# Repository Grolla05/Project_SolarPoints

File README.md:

# 💡 Project Solar Points — Smart Lighting for Low-Infrastructure Areas

> Light where there’s no infrastructure. Safety through simplicity and efficiency.

---

## 🌙 O que é o Solar Points?

O **Solar Points** é um sistema de iluminação pública autônomo e inteligente pensado para locais com pouca ou nenhuma infraestrutura elétrica, como:

- Paradas de ônibus
- Vielas e ruas estreitas
- Praças públicas
- Regiões periféricas e isoladas
- Áreas externas de residências

O objetivo permanece o mesmo: aumentar a segurança e o bem-estar comunitário com uma solução de baixo custo, sustentável e de fácil manutenção.

---

## 🔁 Evolução do projeto: de totalmente analógico para arquitetura digital

Inicialmente o projeto foi concebido como **100% analógico** (apenas componentes discretos e circuitos analógicos). Com as necessidades de sensoriamento mais preciso, flexibilidade operacional e otimização de consumo, o projeto evoluiu para uma **arquitetura digital/híbrida** baseada em microcontrolador e periféricos.

Essa mudança preserva os princípios de simplicidade, robustez e baixo consumo, ao mesmo tempo que agrega capacidades importantes:

- **Leitura digital de sensores** (intensidade de luz, distância/presença)
- **Decisões e temporizações programáveis** via firmware leve
- **Gerenciamento inteligente de energia** (controle de conversores DC-DC, modos de sono)
- **Comunicação entre módulos** via I2C/GPIO quando necessário

> A imagem anexada ao repositório ilustra o bloco funcional do novo design: microcontrolador central, sensores de luz e distância, gerenciamento de energia, baterias e conversores DC-DC.

---

## ⚙️ Principais funcionalidades (atualizado)

- **Ativação automática** baseada em sensores de luminosidade e presença
- **Modos ajustáveis** via firmware (p.ex. sensibilidades, temporização)
- **Operação autônoma** com painéis solares e baterias
- **Gestão adequada de energia** com conversores DC-DC e técnicas de baixo consumo
- **Projeto modular e replicável** com possibilidade de atualização de firmware

---

## 🛠️ Tecnologias e componentes (atualizado)

- **Microcontrolador** (unidade central de controle) — responsável por leitura de sensores e lógica de acionamento
- **Sensor de luminosidade** (LDR/photodiode + ADC) — medida de intensidade luminosa
- **Sensor de distância/presença** (ultrassom/IR) — detectar passagem ou presença
- **Conversores DC-DC** (step-up/step-down) — fornecimento estável para LEDs e eletrônica
- **Gestão de energia / Power Management** (monitoramento de bateria, carregamento solar)
- **Bateria recarregável e painéis solares**
- **LEDs de potência** para iluminação pública
- **Interfaces**: GPIOs para sinalização/controle, I2C para sensores/power ICs quando aplicável

---

## 🔍 Diagrama funcional

O diagrama no repositório mostra os blocos principais interconectados:

- 1 — Baterias (alimentação)
- 4 — Power Management (monitoramento/carregador)
- 11 — Conversão DC-DC (alimentação dos LEDs e eletrônica)
- 2 — Microcontrolador (núcleo lógico)
- 5 — Medição de intensidade luminosa (sensor)
- 6 — Sensor de distância/presença
- 3 — LED de status / power

O microcontrolador realiza a lógica central: lê sensores (GPIOs/ADC/I2C), decide quando ligar os LEDs e controla os conversores para otimizar consumo.

---

## ✨ Aplicações no mundo real

O Solar Points continua ideal para iluminar pontos sem infraestrutura elétrica: pontos de ônibus, caminhos em áreas rurais, entradas de condomínios e outras localidades onde uma solução autônoma e resiliente faz diferença.

---

## 👥 Autores

Desenvolvido por:

- **Felipe Grolla Freitas** – Engenharia de Controle e Automação (PUC-Campinas)
- **Guilherme Oliveira Nogueira** – Engenharia de Controle e Automação (PUC-Campinas)
- **Giovanna Lima Salvagnini** – Engenharia de Controle e Automação (PUC-Campinas)
- **Henrique Spadaccia Chambó** – Engenharia de Controle e Automação (PUC-Campinas)

---

> 🧠 "A simplicidade, aliada a decisões digitais pontuais, amplia o impacto das soluções de engenharia em contextos reais."

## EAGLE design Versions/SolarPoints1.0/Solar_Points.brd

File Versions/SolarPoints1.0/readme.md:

# First version of the project (Solar Point with only analog circuit)
## Schematc circuit diagram

## BRD Circuit file

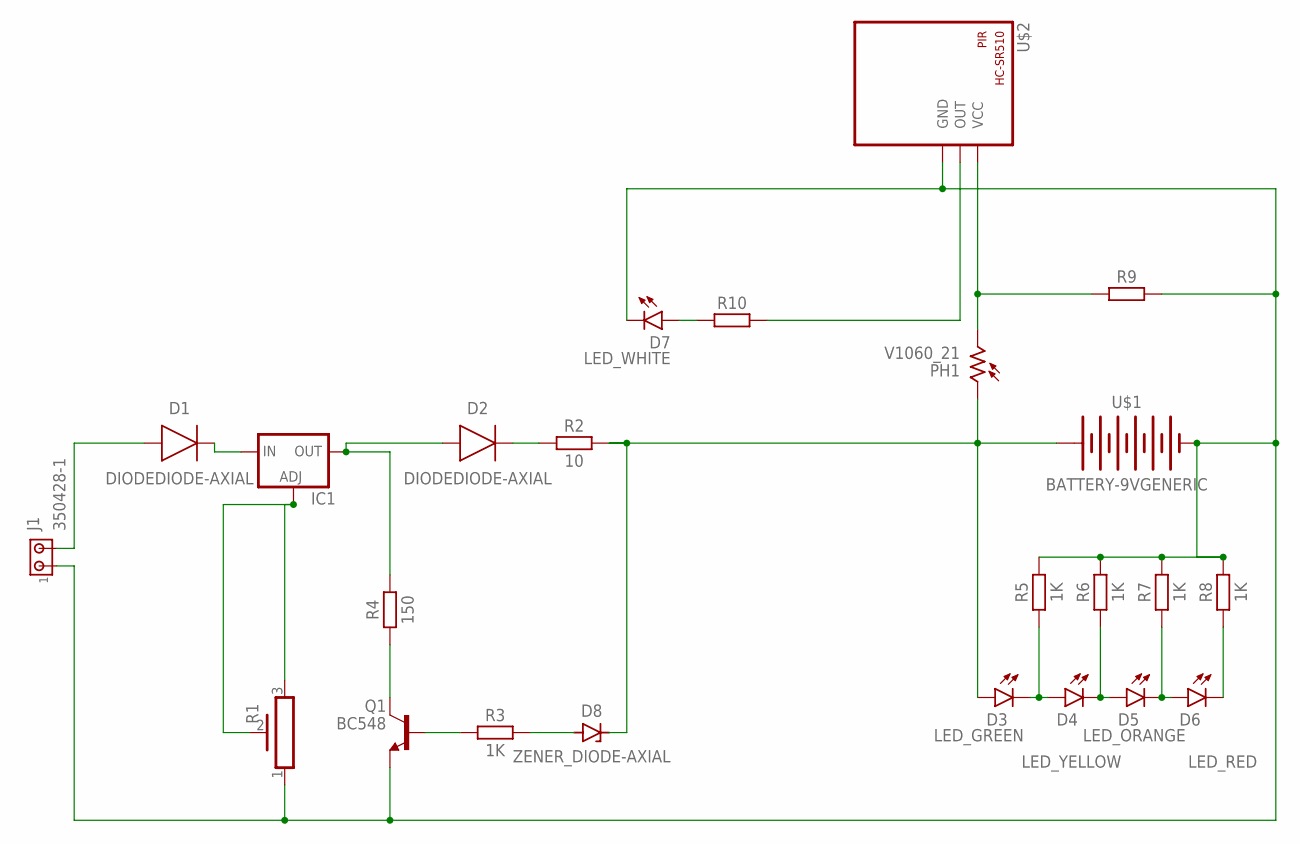
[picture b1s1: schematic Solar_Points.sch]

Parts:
D1, D2: DIODEDIODE-AXIAL; DIODE-AXIAL
D3: LED_GREEN; LEDRD254W60D565H860B_G
D4: LED_YELLOW; LEDRD254W60D565H860B_Y
D5: LED_ORANGE; LEDRD254W60D565H860B_O
D6: LED_RED; LEDRD254W60D565H860B
D7: LED_WHITE; LEDRD254W60D565H860B_W
D8: ZENER_DIODE-AXIAL; DIODE-AXIAL
IC1: LM317TL; 317TL
J1: 350428-1
PH1: V1060_21; TO-5_V10
Q1: BC548; TO92
R1: POT_PV36Z; PV36Z
R2: 10; RESAD1176W63L850D250B
R3, R5, R6, R7, R8: 1K; RESAD1176W63L850D250B
R4: 150; RESAD1176W63L850D250B
R9, R10: RESISTOR__AXIAL-11.7MM-PITCH; RESAD1176W63L850D250B
U$1: BATTERY-9VGENERIC; BATTERY-GENERIC
U$2: HC-SR501

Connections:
unnamed: D1.1 (A), J1.2
unnamed: Q1.1 (C), R4.1
unnamed: Q1.2 (B), R3.1
unnamed: D1.2 (C), IC1.3 (IN)
unnamed: D3.2 (C), D4.1 (A), R5.1
unnamed: D2.2 (C), R2.1
unnamed: D3.1 (A), D8.2 (C), PH1.1, R2.2, U$1.+
unnamed: D7.1 (A), R10.1
unnamed: D4.2 (C), D5.1 (A), R6.1
unnamed: PH1.2, R9.1, U$2.VCC
unnamed: D5.2 (C), D6.1 (A), R7.1
unnamed: R10.2, U$2.OUT
unnamed: D6.2 (C), R8.1
unnamed: D7.2 (C), J1.1, Q1.3 (E), R1.1, R5.2, R6.2, R7.2, R8.2, R9.2, U$1.-, U$2.GND
unnamed: D8.1 (A), R3.2
unnamed: D2.1 (A), IC1.2 (OUT), R4.2
unnamed: IC1.1 (ADJ), R1.2, R1.3

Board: 2 copper layers, 24 parts (0 on the bottom side), 17 nets, no tracks yet.

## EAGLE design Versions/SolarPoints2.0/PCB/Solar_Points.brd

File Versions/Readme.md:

## This folder serves to archive all iterations of the project since 2025.

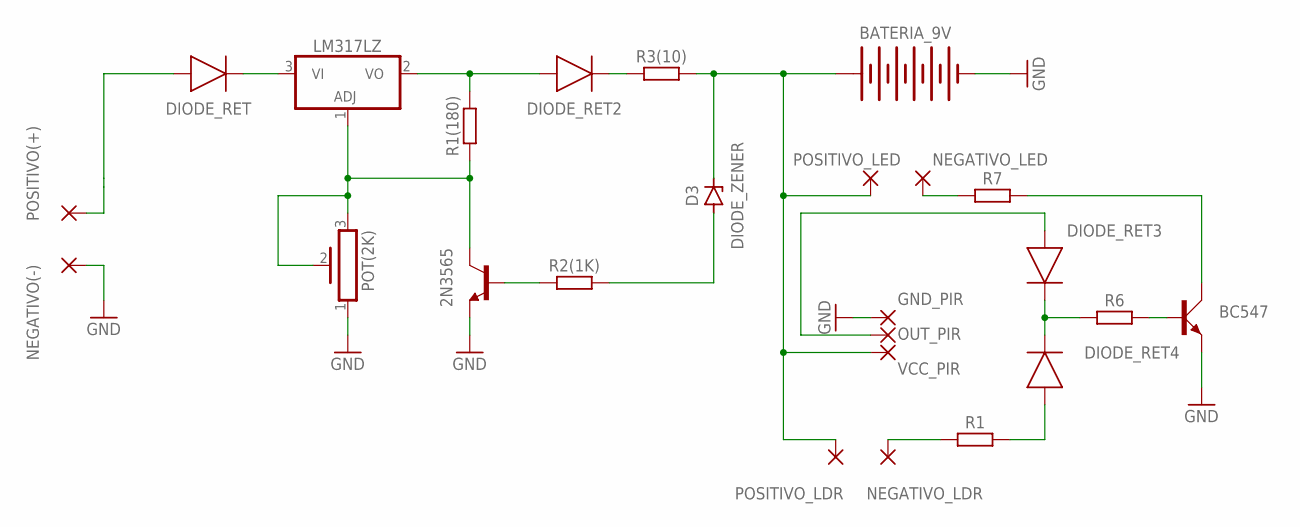
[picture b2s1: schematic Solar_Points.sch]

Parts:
2N3565: 2N3565; TO92
BATERIA_9V: BATTERY-9VGENERIC; BATTERY-GENERIC
BC547: BC547; SOT54A
D3: DIODE_ZENER; DIODE-AXIAL
DIODE_RET, DIODE_RET2, DIODE_RET3, DIODE_RET4: DIODEDIODE-AXIAL; DIODE-AXIAL
GND_PIR: 1,6/0,8
LM317LZ: LM317LZ; TO92
NEGATIVO(-): 3,81/1,4
NEGATIVO_LDR: 1,6/0,8
NEGATIVO_LED: 2,15/1,0
OUT_PIR: 1,6/0,8
POSITIVO(+): 3,81/1,4
POSITIVO_LDR: 1,6/0,8
POSITIVO_LED: 2,15/1,0
POT(2K): POT_HA-06; HA-06-SM065
R1, R1(180), R2(1K), R3(10), R6, R7: RESISTOR_AXIAL-10.16MM-PITCH; RESAD1016W63L850D250B
VCC_PIR: 1,6/0,8

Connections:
GND: 2N3565.3 (E), BATERIA_9V.-, BC547.E, GND_PIR.1, NEGATIVO(-).1, POT(2K).1
unnamed: DIODE_RET.1 (A), POSITIVO(+).1
unnamed: DIODE_RET.2 (C), LM317LZ.3 (VI)
unnamed: 2N3565.1 (C), LM317LZ.1 (ADJ), POT(2K).2, POT(2K).3, R1(180).1
unnamed: DIODE_RET2.1 (A), LM317LZ.2 (VO), R1(180).2
unnamed: DIODE_RET2.2 (C), R3(10).2
unnamed: BATERIA_9V.+, D3.2 (C), POSITIVO_LDR.1, POSITIVO_LED.1, R3(10).1, VCC_PIR.1
unnamed: D3.1 (A), R2(1K).1
unnamed: 2N3565.2 (B), R2(1K).2
unnamed: DIODE_RET3.1 (A), OUT_PIR.1
unnamed: NEGATIVO_LED.1, R7.1
unnamed: NEGATIVO_LDR.1, R1.1
unnamed: DIODE_RET3.2 (C), DIODE_RET4.2 (C), R6.1
unnamed: BC547.B, R6.2
unnamed: BC547.C, R7.2
unnamed: DIODE_RET4.1 (A), R1.2

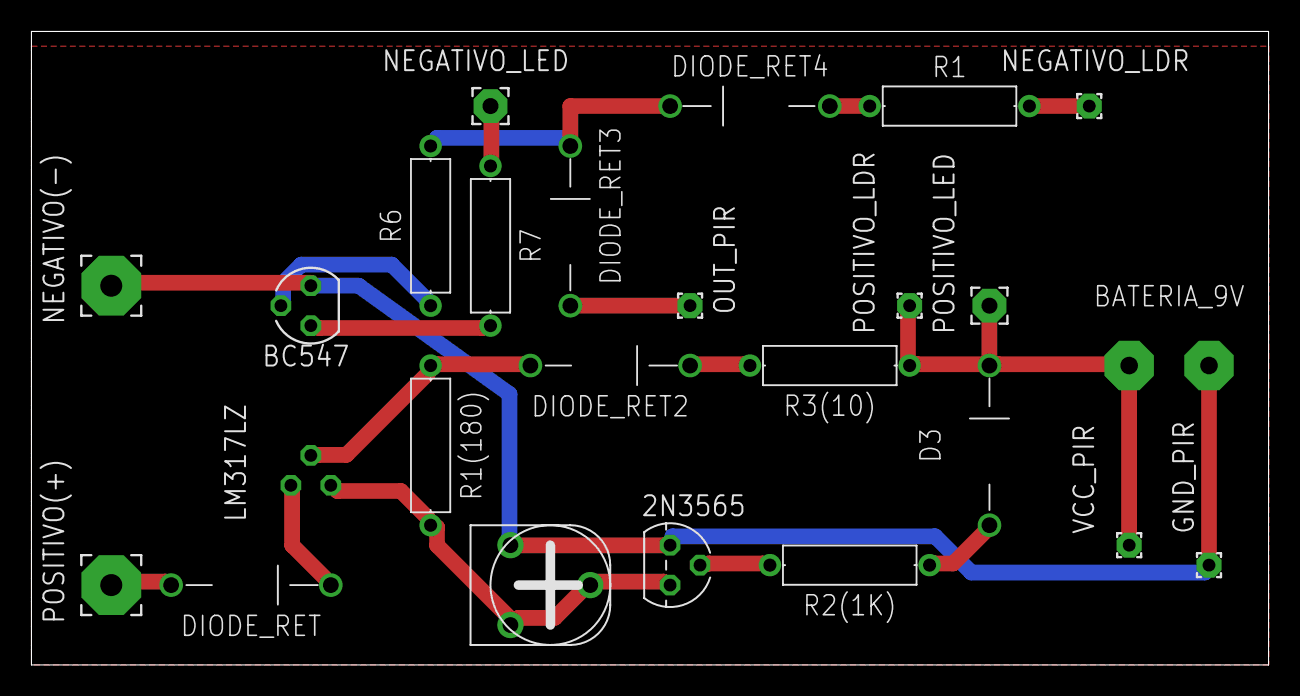
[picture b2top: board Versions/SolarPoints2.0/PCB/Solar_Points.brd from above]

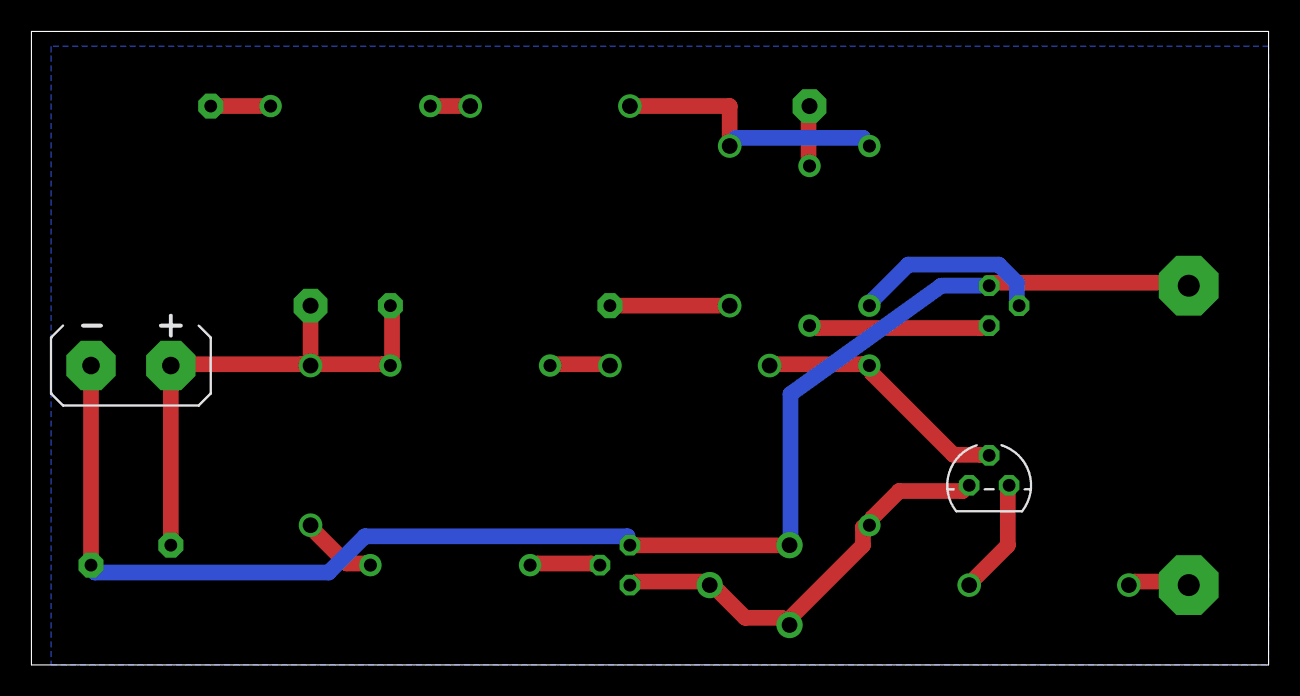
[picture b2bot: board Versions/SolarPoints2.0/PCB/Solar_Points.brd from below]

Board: 2 copper layers, 78.7 x 40.3 mm, 25 parts (2 on the bottom side), 16 nets.

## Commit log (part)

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2025-05-10 Rename LINCENSE.txt to LICENSE.txt
2025-05-11 Update the finally circuit
2025-05-11 Rename image.png to First_version.png
2025-05-13 Rename image.png to BRD_circuit_image.png
2025-05-13 update files
2025-05-19 update test
2025-06-03 update feat
2025-06-14 Rename image.png to PCB.png
2025-06-14 Rename image.png to Schematics.png
2025-08-27 feat & style
2025-08-27 bug & docs
2025-08-28 feat
2025-09-04 docs
2025-09-08 style
2025-09-08 bug & perf
